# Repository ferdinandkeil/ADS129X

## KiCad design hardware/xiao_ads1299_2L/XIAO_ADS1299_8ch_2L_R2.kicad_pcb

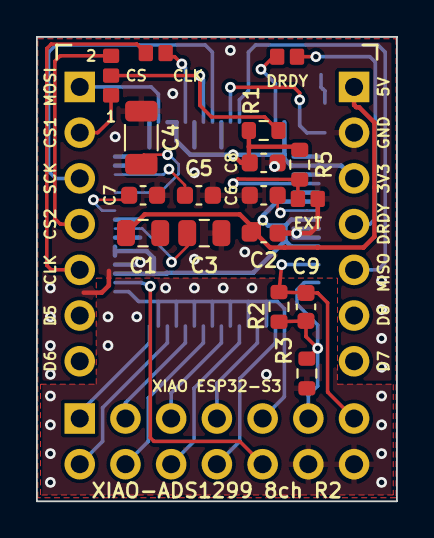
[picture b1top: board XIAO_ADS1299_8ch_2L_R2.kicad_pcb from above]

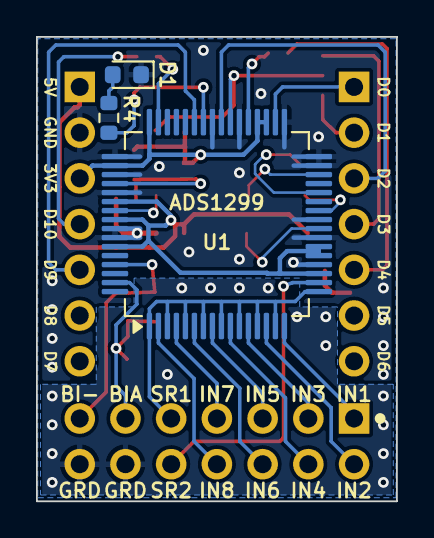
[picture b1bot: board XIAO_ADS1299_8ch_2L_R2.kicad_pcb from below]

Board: 2 copper layers, 20.0 x 25.8 mm, 23 parts (4 on the bottom side), 34 nets.

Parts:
C1, C3: 10u; C_0805_2012Metric
C2, C5, C6, C7, C8: 1u; C_0603_1608Metric
C4: 100u; C_1206_3216Metric
C9: 1.5n C0G; C_0603_1608Metric
D1: LED; LED_0603_1608Metric
J1: XIAO D0-D6; PinHeader_1x07_P2.54mm_Vertical
J2: XIAO 5V..D7; PinHeader_1x07_P2.54mm_Vertical
J3: Out 2x7 RA; PinHeader_2x07_P2.54mm_Horizontal
JP1: CS: D1 / D3; SJ3
JP2: CLK to D4; SJ2
JP3: CLKSEL to GND (ext clock); SJ2
JP4: DRDY to D10; SJ2
R1, R5: 10k; R_0603_1608Metric
R2: 1M; R_0603_1608Metric
R3: 4.7k; R_0603_1608Metric
R4: 3.3k; R_0603_1608Metric
U1: ADS1299IPAG; TQFP-64_10x10mm_P0.5mm

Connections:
AVDD: C1.1, C2.1, J2.1, U1.19, U1.21, U1.22, U1.54, U1.56, U1.59
BIASINV: C9.1, J3.13, R2.1, U1.61
BIASOUT: C9.2, J3.11, R2.2, R3.1, U1.63
CLK: JP2.2, U1.37
CLKSEL: JP3.1, R5.1, U1.52
CS: JP1.2, R1.2, U1.39
DRDY: JP4.1, U1.47
DVDD: C8.1, J2.3, R1.1, R5.2, U1.35, U1.36, U1.48, U1.50
GND: C1.2, C2.2, C3.2, C4.2, C5.2, C6.2, C7.2, C8.2, D1.1, J2.2, JP3.2, U1.20, U1.23, U1.25, U1.31, U1.32, U1.33, U1.38, U1.41, U1.49, U1.51, U1.53, U1.57, U1.58
GPIO1: R4.1, U1.42
GUARD: J3.12, J3.14, R3.2
IN1P: J3.1, U1.16
IN2P: J3.2, U1.14
IN3P: J3.3, U1.12
IN4P: J3.4, U1.10
IN5P: J3.5, U1.8
IN6P: J3.6, U1.6
IN7P: J3.7, U1.4
IN8P: J3.8, U1.2
LED_A: D1.2, R4.2
MISO: J2.5, U1.43
MOSI: J1.1, U1.34
SCK: J1.3, U1.40
SRB1: J3.9, U1.1, U1.3, U1.5, U1.7, U1.9, U1.11, U1.13, U1.15, U1.17
SRB2: J3.10, U1.18
VCAP1: C4.1, U1.28
VCAP2: C5.1, U1.30
VCAP3: C6.1, U1.55
VCAP4: C7.1, U1.26
VREFP: C3.1, U1.24
XCLK: J1.5, JP2.1
XCS1: J1.2, JP1.1
XCS2: J1.4, JP1.3
XDRDY: J2.4, JP4.2

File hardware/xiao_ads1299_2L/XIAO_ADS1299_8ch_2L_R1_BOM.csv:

Refs,Qty,Value / part,Footprint,Side
C1 C3,2,10u,C_0805_2012Metric,Top (XIAO side)
C2 C5 C6 C7 C8,5,1u,C_0603_1608Metric,Top (XIAO side)
C4,1,100u,C_1206_3216Metric,Top (XIAO side)
C9,1,1.5 nF C0G 0603,C_0603_1608Metric,Top (XIAO side)
D1,1,LED 0603,LED_0603_1608Metric,Bottom (ADS side)
J1,1,1x7 2.54 mm socket/header for XIAO (D0-D6),PinHeader_1x07_P2.54mm_Vertical,Top (XIAO side)
J2,1,1x7 2.54 mm socket/header for XIAO (5V..D7),PinHeader_1x07_P2.54mm_Vertical,Top (XIAO side)
J3,1,2x6 2.54 mm right-angle pin header,PinHeader_2x06_P2.54mm_Horizontal,Bottom (ADS side)
R1,1,10k,R_0603_1608Metric,Top (XIAO side)
R2,1,1M,R_0603_1608Metric,Top (XIAO side)
R3,1,4.7k,R_0603_1608Metric,Top (XIAO side)
R4,1,3.3k,R_0603_1608Metric,Bottom (ADS side)
U1,1,ADS1299IPAG (TQFP-64); ADS1299-6 also fits,TQFP-64_10x10mm_P0.5mm,Bottom (ADS side)

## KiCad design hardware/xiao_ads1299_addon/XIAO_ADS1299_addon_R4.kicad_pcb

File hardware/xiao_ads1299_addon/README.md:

# XIAO ADS1299 add-on, channels 9–16, R6.2 (18-pin flex inputs)

**R6.2** is the 18-pin flex board with every via moved off component pads. Earlier revisions: R6. Parts and placement are unchanged. **One pinout change:** the ADS clock between stacked boards moved from D6 to D1, and the silkscreen is relabelled to match. Main and add-on boards of the same revision must be used together.

## R6.2 changes: vias off pads
A via on or touching a small pad can wick solder away from the joint. On 0.5 mm-pitch pins its ring can also bridge to the next pin.

- **New positions:** each via now sits beside its pad, joined by a short straight or 45° trace.
- **Re-joined traces:** traces that met the via are re-routed from their previous corner, straight and at 45°.
- **Checks:** the design-rule report matches the original board's line for line, nothing is unconnected, and `tools/check_via_in_pad.py` finds no via in any part pad.
- **"Drill clear" rows** in the table: the hole is off the pad and the ring still touches the pad edge. Vias are tented, so no solder reaches the hole.

| Pad | Net | Via moved | Distance | Result |
|---|---|---|---|---|
| C5.2 | GND | (-3.00, -3.60) → (-2.92, -3.47) | 0.15 mm | clear |
| C8.2 | GND | (2.20, -3.20) → (1.89, -2.75) | 0.55 mm | clear |
| C9.2 | GND | (2.60, -4.20) → (1.92, -4.38) | 0.70 mm | clear |
| C4.2 | GND | (-1.60, -1.60) → (-0.69, -2.02) | 1.00 mm | clear |
| C3.2 | GND | (-2.40, 0.40) → (-2.11, 0.06) | 0.45 mm | clear |
| C5.1 | VCAP2 | (-4.65, -4.93) → (-4.49, -5.12) | 0.25 mm | clear |
| C9.1 | DVDD | (3.60, -4.20) → (3.52, -3.91) | 0.30 mm | clear |

`plots/*_via_check.png` shows pads and vias, before and after.

## XIAO nRF54L15

The XIAO pins match every XIAO, including the nRF54L15, and SPI sits on that board's high-speed SPI:

| XIAO pin | nRF54L15 | Use here |
|---|---|---|
| D8 / D9 / D10 | P2.01 / P2.04 / P2.02 | SCK / MISO / MOSI on **SPIM00** (Zephyr `xiao_spi` = `&spi00`) |
| D0 | P1.04 | DRDY (main). P1 supports pin interrupts; P2 GPIOs don't |
| D3 | P1.07 | CS (main) |
| D7 | P2.07 | CS2 (add-on) |
| D4 / D5 | P1.10 / P1.11 | I²C (`i2c22`), main board only |
| D1 | P1.05 | ADS clock pass-through between stacked boards (moved from D6 in this revision) |

- **D6 is free now.** The clock used to share D6 with the UART TX that Zephyr enables by default (`uart21`), so it moved to D1. With an add-on fitted, D7 is CS2, so disable `uart21` then: `&uart21 { status = "disabled"; };`.
- **USB power only:** AVDD comes from the XIAO 5 V pin through FB1, and that pin carries no usable 5 V when the XIAO runs on battery alone.

## Inputs, aux header and guard
See [`../FLEX18.md`](../FLEX18.md): 18-pin Hirose FH12 flex input, 2×3 1.27 mm aux header, and closed guard on all four layers.

## Files
| File | Contents |
|---|---|
| `XIAO_ADS1299_addon_R6.2.kicad_pcb` / `.kicad_pro` | KiCad 7 board and rules |
| `gerber/` | Gerbers and drill file (4 layers) |
| `XIAO_ADS1299_addon_R6.2_BOM.csv` | Bill of materials |
| `plots/` | Top/bottom view, copper by net, via check |

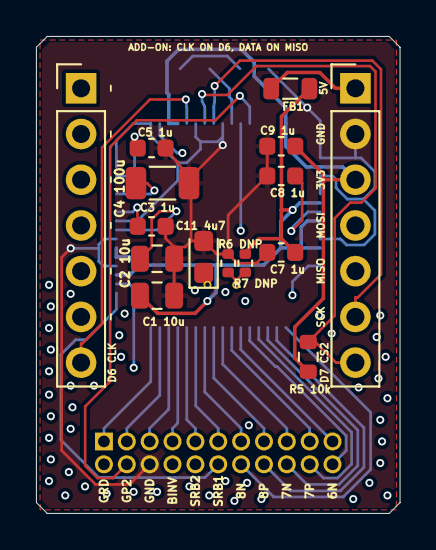
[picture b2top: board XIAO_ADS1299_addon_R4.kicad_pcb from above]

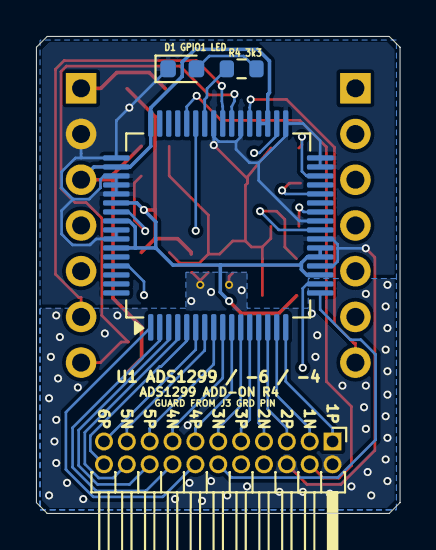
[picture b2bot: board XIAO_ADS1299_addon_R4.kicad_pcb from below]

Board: 4 copper layers, 20.2 x 26.5 mm, 21 parts (4 on the bottom side), 37 nets.

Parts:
C1, C2: 10u; C_0805_2012Metric
C3, C5, C7, C8, C9: 1u; C_0603_1608Metric
C4: 100u; C_1206_3216Metric
C11: 4.7u 10V tant; CP_EIA-2012-12_Kemet-R
D1: LED; LED_0603_1608Metric
FB1: 600R@100MHz; L_0805_2012Metric
GV1, GV2: guard via; GuardVia
J1: XIAO left (pass-through); PinHeader_1x07_P2.54mm_Vertical
J2: XIAO right (pass-through); PinHeader_1x07_P2.54mm_Vertical
J3: TFM-111 2x11 1.27mm RA; PinHeader_2x11_P1.27mm_Horizontal
R4: 3.3k; R_0603_1608Metric
R5: 10k; R_0603_1608Metric
R6, R7: 200k; R_0402_1005Metric
U1: ADS1299IPAG (or -6 / -4); TQFP-64_10x10mm_P0.5mm

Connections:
+5V: FB1.1, J2.1
AVDD: C1.1, C7.1, FB1.2, R6.2, U1.19, U1.21, U1.22, U1.54, U1.56, U1.59
BIASINV: J3.8, U1.61
CLK: J1.7, U1.37
CS2: J2.7, R5.2, U1.39
DVDD: C9.1, J2.3, R5.1, U1.35, U1.36, U1.48, U1.50
GND: C1.2, C2.2, C3.2, C4.2, C5.2, C7.2, C8.2, C9.2, C11.2, D1.1, J2.2, J3.6, R7.2, U1.20, U1.23, U1.25, U1.31, U1.32, U1.33, U1.38, U1.41, U1.49, U1.51, U1.52, U1.53, U1.57, U1.58
GPIO1: R4.1, U1.42
GPIO2: J3.4, U1.44
GUARD: C11.1, GV1.1, GV2.1, J3.2, R6.1, R7.1
IN1N: J3.3, U1.15
IN1P: J3.1, U1.16
IN2N: J3.7, U1.13
IN2P: J3.5, U1.14
IN3N: J3.11, U1.11
IN3P: J3.9, U1.12
IN4N: J3.15, U1.9
IN4P: J3.13, U1.10
IN5N: J3.19, U1.7
IN5P: J3.17, U1.8
IN6N: J3.22, U1.5
IN6P: J3.21, U1.6
IN7N: J3.18, U1.3
IN7P: J3.20, U1.4
IN8N: J3.14, U1.1
IN8P: J3.16, U1.2
LED_A: D1.2, R4.2
MISO: J2.5, U1.43
MOSI: J2.4, U1.34
SCK: J2.6, U1.40
SRB1: J3.12, U1.17
SRB2: J3.10, U1.18
VCAP1: C4.1, U1.28
VCAP2: C5.1, U1.30
VCAP3: C8.1, U1.55
VCAP4: C3.1, U1.26
VREFP: C2.1, U1.24

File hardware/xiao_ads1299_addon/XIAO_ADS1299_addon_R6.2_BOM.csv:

Refs,Qty,Value / part,Footprint,Side
C1 C2,2,10u,C_0805_2012Metric,Top
C3 C5 C7 C8 C9,5,1u,C_0603_1608Metric,Top
C4,1,100u,C_1206_3216Metric,Top
C11,1,4.7u 10V tant,CP_EIA-2012-12_Kemet-R,Top
D1,1,LED,LED_0603_1608Metric,Bottom
FB1,1,600R@100MHz,L_0805_2012Metric,Top
J1,1,XIAO left (pass-through),PinHeader_1x07_P2.54mm_Vertical,Top
J2,1,XIAO right (pass-through),PinHeader_1x07_P2.54mm_Vertical,Top
J3,1,FH12-18S-0.5SH(55),Hirose_FH12-18S-0.5SH_1x18-1MP_P0.50mm_Horizontal,Bottom
J4,1,2x3 1.27mm,PinHeader_2x03_P1.27mm_Vertical,Bottom
R4,1,3.3k,R_0603_1608Metric,Bottom
R5,1,10k,R_0603_1608Metric,Top
R6 R7,2,200k,R_0402_1005Metric,Top
U1,1,ADS1299IPAG (or -6 / -4),TQFP-64_10x10mm_P0.5mm,Bottom

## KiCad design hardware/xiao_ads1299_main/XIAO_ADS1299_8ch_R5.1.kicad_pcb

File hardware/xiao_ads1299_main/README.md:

# XIAO ADS1299 main board, 8 channels, R5.2 (18-pin flex inputs)

**R5.2** is the 18-pin flex board with every via moved off component pads. Earlier revisions: R5. Parts and placement are unchanged. **One pinout change:** the ADS clock between stacked boards moved from D6 to D1, and the silkscreen is relabelled to match. Main and add-on boards of the same revision must be used together.

## R5.2 changes: vias off pads
A via on or touching a small pad can wick solder away from the joint. On 0.5 mm-pitch pins its ring can also bridge to the next pin.

- **New positions:** each via now sits beside its pad, joined by a short straight or 45° trace.
- **Re-joined traces:** traces that met the via are re-routed from their previous corner, straight and at 45°.
- **Checks:** the design-rule report matches the original board's line for line, nothing is unconnected, and `tools/check_via_in_pad.py` finds no via in any part pad.
- **"Drill clear" rows** in the table: the hole is off the pad and the ring still touches the pad edge. Vias are tented, so no solder reaches the hole.
- **U1 pin 25:** the only spot was 1.5 mm out past the pin tip, between the pin row and J1 pin 4. Its stub can't be straight or 45° there with 0.15 mm clearance, so it's one short angled run on the bottom.

| Pad | Net | Via moved | Distance | Result |
|---|---|---|---|---|
| U1.33 | GND | (-4.20, -5.66) → (-4.25, -5.66) | 0.05 mm | clear |
| U1.32 | GND | (-5.50, -3.80) → (-5.82, -4.25) | 0.55 mm | clear |
| D1.1 | GND | (1.25, -8.55) → (1.31, -7.85) | 0.70 mm | clear |
| C4.2 | GND | (-1.70, -1.40) → (-1.65, -1.10) | 0.30 mm | clear |
| C7.2 | GND | (2.85, 1.60) → (3.35, 1.60) | 0.50 mm | drill clear |
| C8.2 | GND | (2.70, -2.40) → (2.74, -1.90) | 0.50 mm | clear |
| U1.25 | GND | (-5.66, -0.25) → (-6.89, -1.11) | 1.50 mm | clear |
| C3.2 | GND | (-2.90, 0.40) → (-2.13, 0.04) | 0.85 mm | clear |
| C4.2 | GND | (-2.50, -2.00) → (-2.56, -2.35) | 0.35 mm | clear |
| R6.2 | GND | (0.46, 0.00) → (0.45, -0.10) | 0.10 mm | drill clear |
| C11.2 | GND | (1.30, -1.40) → (1.85, -0.22) | 1.30 mm | clear |
| R7.1 | GUARD | (4.50, 10.00) → (4.49, 9.90) | 0.10 mm | clear |

`plots/*_via_check.png` shows pads and vias, before and after.

## XIAO nRF54L15

The XIAO pins match every XIAO, including the nRF54L15, and SPI sits on that board's high-speed SPI:

| XIAO pin | nRF54L15 | Use here |
|---|---|---|
| D8 / D9 / D10 | P2.01 / P2.04 / P2.02 | SCK / MISO / MOSI on **SPIM00** (Zephyr `xiao_spi` = `&spi00`) |
| D0 | P1.04 | DRDY (main). P1 supports pin interrupts; P2 GPIOs don't |
| D3 | P1.07 | CS (main) |
| D7 | P2.07 | CS2 (add-on) |
| D4 / D5 | P1.10 / P1.11 | I²C (`i2c22`), main board only |
| D1 | P1.05 | ADS clock pass-through between stacked boards (moved from D6 in this revision) |

- **D6 is free now.** The clock used to share D6 with the UART TX that Zephyr enables by default (`uart21`), so it moved to D1. With an add-on fitted, D7 is CS2, so disable `uart21` then: `&uart21 { status = "disabled"; };`.
- **USB power only:** AVDD comes from the XIAO 5 V pin through FB1, and that pin carries no usable 5 V when the XIAO runs on battery alone.

## Inputs, aux header and guard
See [`../FLEX18.md`](../FLEX18.md): 18-pin Hirose FH12 flex input, 2×3 1.27 mm aux header, and closed guard on all four layers.

## Files
| File | Contents |
|---|---|
| `XIAO_ADS1299_8ch_R5.2.kicad_pcb` / `.kicad_pro` | KiCad 7 board and rules |
| `gerber/` | Gerbers and drill file (4 layers) |
| `XIAO_ADS1299_8ch_R5.2_BOM.csv` | Bill of materials |
| `plots/` | Top/bottom view, copper by net, via check |

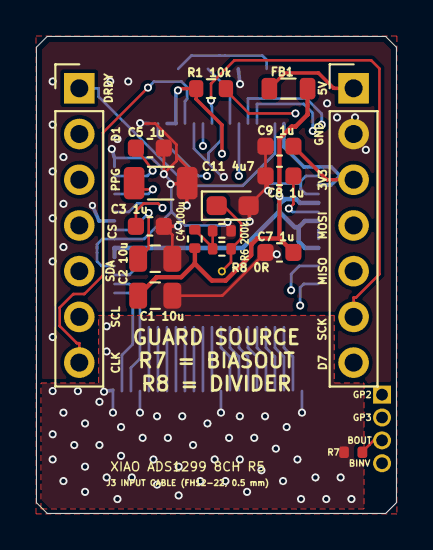
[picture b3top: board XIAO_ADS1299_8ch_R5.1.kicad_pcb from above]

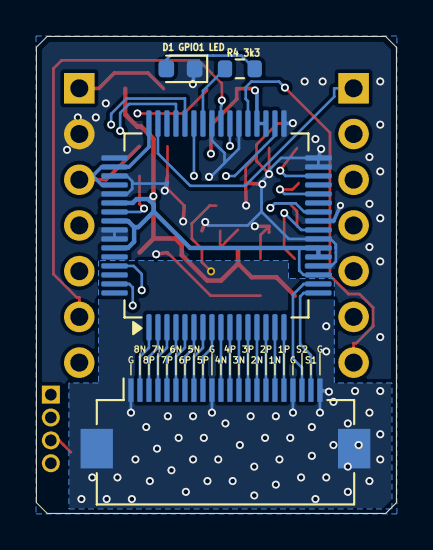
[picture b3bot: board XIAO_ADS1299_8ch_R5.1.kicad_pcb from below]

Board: 4 copper layers, 20.0 x 26.5 mm, 23 parts (5 on the bottom side), 41 nets.

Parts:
C1, C2: 10u; C_0805_2012Metric
C3, C5, C7, C8, C9: 1u; C_0603_1608Metric
C4: 100u; C_1206_3216Metric
C11: 4.7u 10V tant; CP_EIA-2012-12_Kemet-R
D1: LED; LED_0603_1608Metric
FB1: 600R@100MHz; L_0805_2012Metric
GV1: guard via; GuardVia
J1: XIAO left (D0-D6); PinHeader_1x07_P2.54mm_Vertical
J2: XIAO right (5V..D7); PinHeader_1x07_P2.54mm_Vertical
J3: FH12-22S-0.5SH(55); Hirose_FH12-22S-0.5SH_1x22-1MP_P0.50mm_Horizontal
J4: 1x4 1.27mm; PinHeader_1x04_P1.27mm_Vertical
R1: 10k; R_0603_1608Metric
R4: 3.3k; R_0603_1608Metric
R5, R6: 200k; R_0402_1005Metric
R7: 4.7k (BIAS); R_0402_1005Metric
R8: 0R (DIV); R_0402_1005Metric
U1: ADS1299IPAG (or -6 / -4); TQFP-64_10x10mm_P0.5mm

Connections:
+5V: FB1.1, J2.1
AVDD: C1.1, C7.1, FB1.2, R5.1, U1.19, U1.21, U1.22, U1.54, U1.56, U1.59
BIASINV: J4.4, U1.61
BIASOUT: J4.3, R7.2, U1.63
CLK: J1.7, U1.37
CS: J1.4, R1.2, U1.39
DRDY: J1.1, U1.47
DVDD: C9.1, J2.3, R1.1, U1.35, U1.36, U1.48, U1.50, U1.52
GDIV: R5.2, R6.1, R8.1
GND: C1.2, C2.2, C3.2, C4.2, C5.2, C7.2, C8.2, C9.2, C11.2, D1.1, J2.2, R6.2, U1.20, U1.23, U1.25, U1.31, U1.32, U1.33, U1.38, U1.41, U1.49, U1.51, U1.53, U1.57, U1.58
GPIO1: R4.1, U1.42
GPIO2: J4.1, U1.44
GPIO3: J4.2, U1.45
GUARD: C11.1, GV1.1, J3.1, J3.10, J3.19, J3.22, J3.MP, R7.1, R8.2
IN1N: J3.17, U1.15
IN1P: J3.18, U1.16
IN2N: J3.15, U1.13
IN2P: J3.16, U1.14
IN3N: J3.13, U1.11
IN3P: J3.14, U1.12
IN4N: J3.11, U1.9
IN4P: J3.12, U1.10
IN5N: J3.8, U1.7
IN5P: J3.9, U1.8
IN6N: J3.6, U1.5
IN6P: J3.7, U1.6
IN7N: J3.4, U1.3
IN7P: J3.5, U1.4
IN8N: J3.2, U1.1
IN8P: J3.3, U1.2
LED_A: D1.2, R4.2
MISO: J2.5, U1.43
MOSI: J2.4, U1.34
SCK: J2.6, U1.40
SRB1: J3.21, U1.17
SRB2: J3.20, U1.18
VCAP1: C4.1, U1.28
VCAP2: C5.1, U1.30
VCAP3: C8.1, U1.55
VCAP4: C3.1, U1.26
VREFP: C2.1, U1.24
